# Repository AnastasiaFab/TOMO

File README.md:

#### TOMO is a programmable Touch Synthesizer board based on Arduino. 

##### TOMO can sense your touch on many different materials and create sounds to tell people things.

### What is TOMO?

##TO

**TO** means touch. Tomo uses **Swept Frequency Capacitive Sensing (SFCS)** a concept explored by [Disney Research Labs](http://www.disneyresearch.com/) on this [paper](http://www.disneyresearch.com/wp-content/uploads/touchechi2012.pdf). The Arduino implementation is based on the documentation by [ILLUTRON](http://illutron.dk/Instructable-Use-Any-Surface-as-a-Touch-Interface-with-Arduino) and developed by [Cleniem](https://github.com/clemniem). The internal ongoing research on SFCS can be found at [fablabbcn/TouchE](https://github.com/fablabbcn/TouchE).

##MO

**MO** means [Mozzi](http://sensorium.github.io/Mozzi/) an amazing library for sound synthesis library for Arduino developed by [Tim Barrass](http://www.reverberant.com/pp/barrass.htm). This means you can create sounds with it from simple tones to delays and echos. We will soon add *.WAV palying functionality too.

### How is TOMO?

* Small
* Portable
* Easy
* Fun
* and it runs on batteries for a week!

### Project team:

This project was developed with the support of the [EASTN (The European Art-Science-Technology Network)](https://github.com/eastn.eu) at [Fab Lab Barcelona](http://www.fablabbcn.org/). The first real setup was done for the [FAV Festival](http://festivaldesarchitecturesvives.com/) in Monpellier in June 2014.

* [Cleniem](https://github.com/clemniem) 
* [Pral2a](https://github.com/pral2s)
* [Anastasia Pistofidou](https://github.com/anastasiafab)

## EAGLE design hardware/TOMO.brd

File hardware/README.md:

The TOMO board
==============

Check the the Eagles and the PDF schematic for more information. 

Notice the PCB design is done to be milled on a PCB milling machine.

Check the CAM folder for the PNG for [FabModules](http://kokompe.cba.mit.edu/).

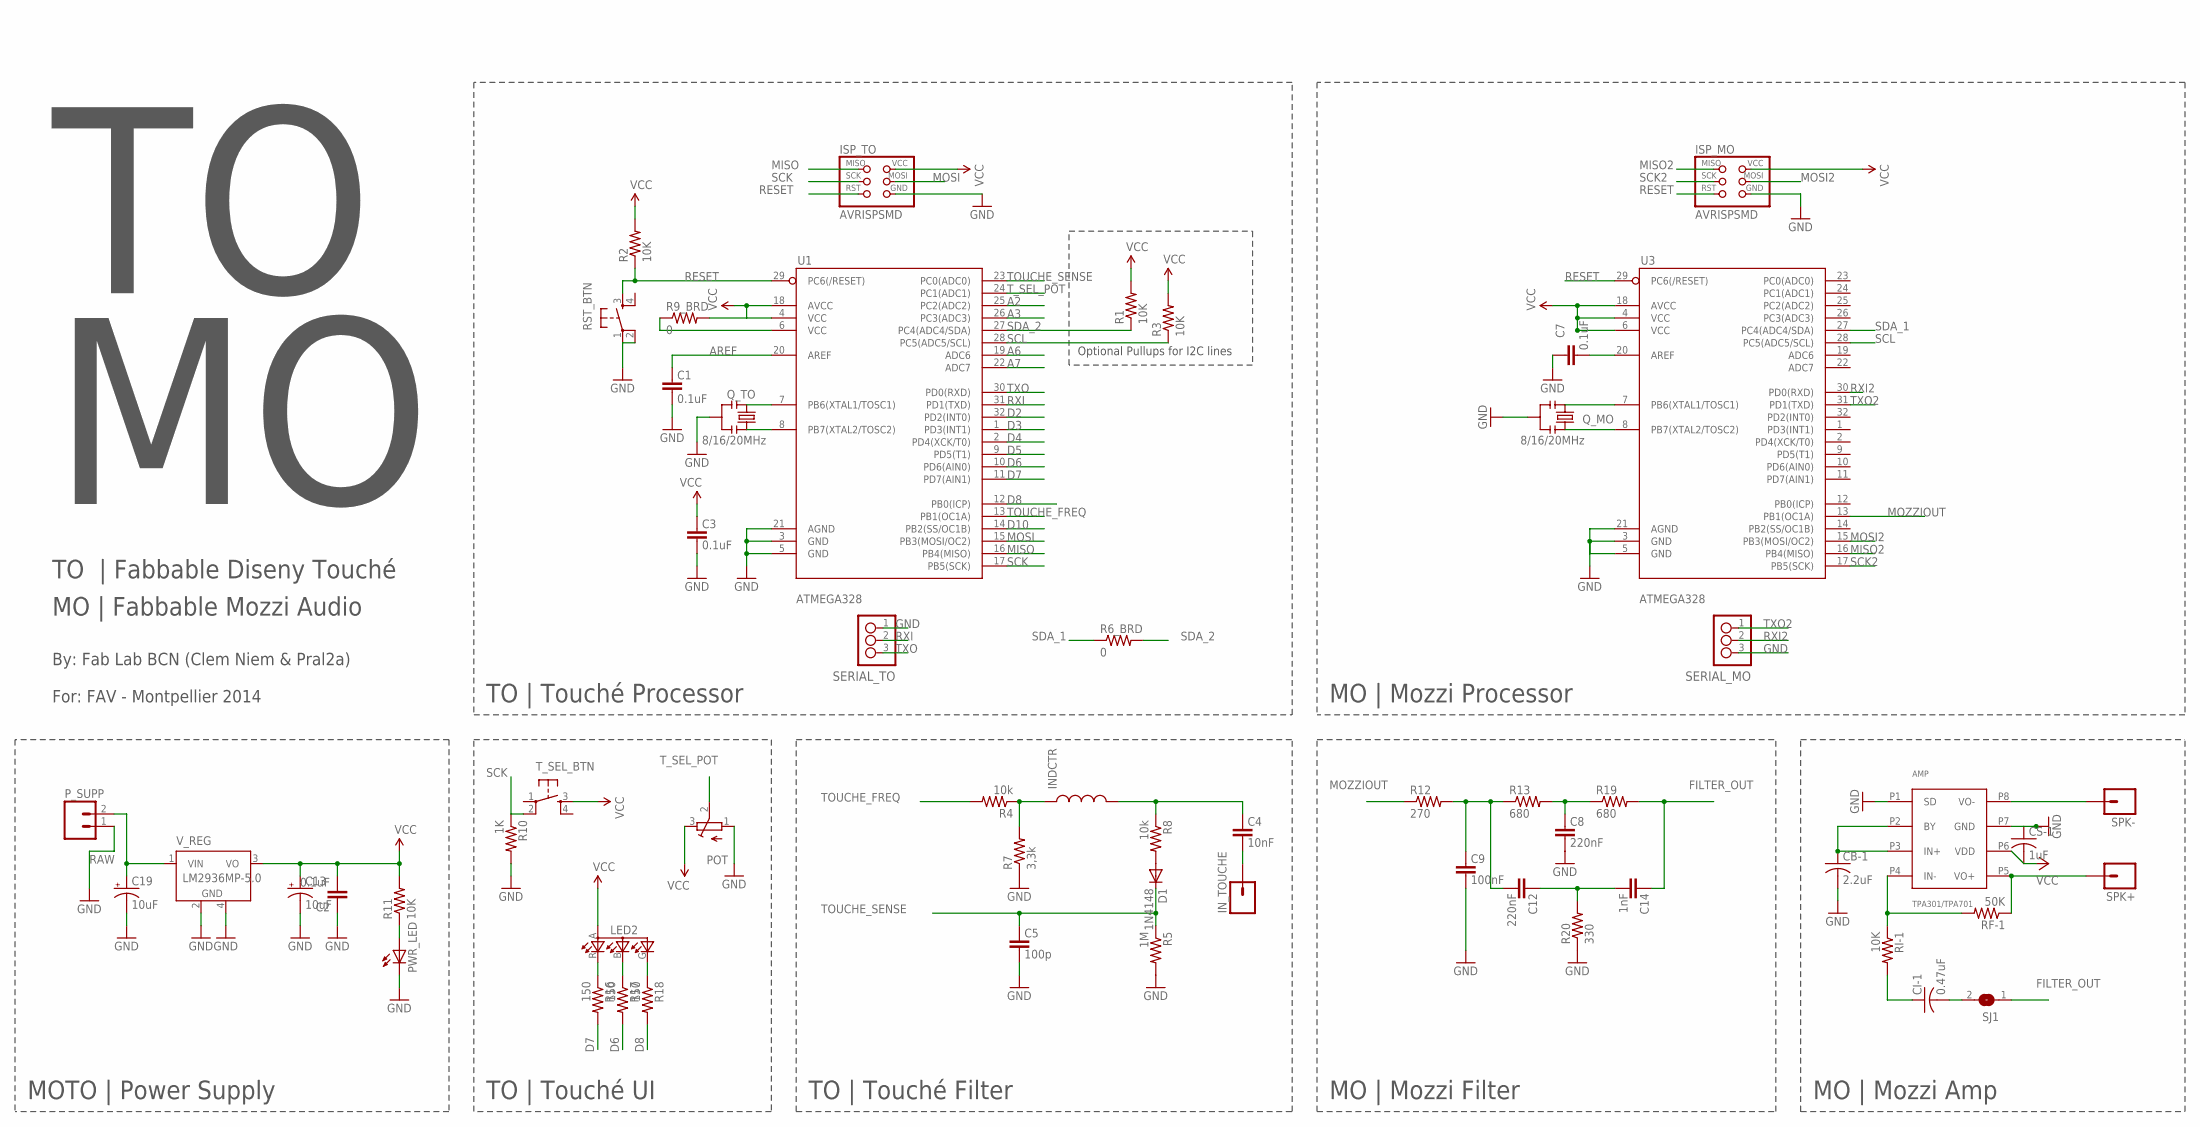
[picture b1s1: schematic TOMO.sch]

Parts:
AMP: TPA301/TPA701; SOIC8
C1, C2, C3, C7: 0.1uF; 1206
C4: 10nF; 1206
C5: 100p; 1206
C8, C12: 220nF; 1206
C9: 100nF; 1206
C13, C19: 10uF; EIA3216
C14: 1nF; 1206
CB-1: 2.2uF; C1206
CI-1: 0.47uF; C1206
CS-1: 1uF; C1206
D1: 1N4148; SOD123
INDCTR: INDUCTOR; CDRH3D28
IN_TOUCHE: M01PTH; 1X01
ISP_MO: AVRISPSMD; 2X03SMD
ISP_TO: AVRISPSMD; 2X03SMD
LED2: LEDRGBOLD; P-LCC-4-3
POT: TRIMPOTTC33X; TC33X
PWR_LED: LED1206; 1206
P_SUPP: M02PTH; 1X02
Q_MO: 8/16/20MHz; RESONATOR-SMD
Q_TO: 8/16/20MHz; RESONATOR-SMD
R1, R2, R3, R11: 10K; 1206
R4, R8: 10k; 1206
R5: 1M; 1206
R6_BRD, R9_BRD: 0; 1206
R7: 3,3k; 1206
R10: 1K; 1206
R12: 270; 1206
R13, R19: 680; 1206
R16, R17, R18: 150; 1206
R20: 330; 0603-RES
RF-1: 50K; R1206
RI-1: 10K; R1206
RST_BTN: 6MM_SWITCH6MM_SWITCH; 6MM_SWITCH
SERIAL_MO: 3_PIN_HEADERHEADER; SMT_PINS_3
SERIAL_TO: 3_PIN_HEADERHEADER; SMT_PINS_3
SJ1: SJW
SPK+: M01PTH; 1X01
SPK-: M01PTH; 1X01
T_SEL_BTN: 6MM_SWITCH6MM_SWITCH; 6MM_SWITCH
U1, U3: ATMEGA328; ATMEGA88THIN
V_REG: LM2936MP-5.0; SOT223

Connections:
A2: U1.25 (PC2(ADC2))
A3: U1.26 (PC3(ADC3))
A6: U1.19 (ADC6)
A7: U1.22 (ADC7)
AREF: C1.2, U1.20 (AREF)
D2: U1.32 (PD2(INT0))
D3: U1.1 (PD3(INT1))
D4: U1.2 (PD4(XCK/T0))
D5: U1.9 (PD5(T1))
D6: R17.2, U1.10 (PD6(AIN0))
D7: R16.2, U1.11 (PD7(AIN1))
D8: R18.2, U1.12 (PB0(ICP))
D10: U1.14 (PB2(SS/OC1B))
FILTER_OUT: C14.2, R19.2, SJ1.1
GND: AMP.P1 (SD), AMP.P7 (GND), C1.1, C2.1, C3.1, C5.1, C7.2, C8.1, C9.1, C13.C (-), C19.C (-), CB-1.2, CS-1.1, ISP_MO.6 (GND), ISP_TO.6 (GND), POT.1 (A), PWR_LED.2 (C), P_SUPP.1, Q_MO.2, Q_TO.2, R5.2, R7.1, R10.2, R20.1, RST_BTN.1, RST_BTN.2 (P1), SERIAL_MO.3, SERIAL_TO.1, U1.3 (GND), U1.5 (GND), U1.21 (AGND), U3.3 (GND), U3.5 (GND), U3.21 (AGND), V_REG.2 (GND), V_REG.4 (GND)
MISO: ISP_TO.1 (MISO), U1.16 (PB4(MISO))
MISO2: ISP_MO.1 (MISO), U3.16 (PB4(MISO))
MOSI: ISP_TO.4 (MOSI), U1.15 (PB3(MOSI/OC2))
MOSI2: ISP_MO.4 (MOSI), U3.15 (PB3(MOSI/OC2))
MOZZIOUT: R12.1, U3.13 (PB1(OC1A))
unnamed: Q_TO.1, U1.8 (PB7(XTAL2/TOSC2))
unnamed: CI-1.2, SJ1.2
unnamed: Q_TO.3, U1.7 (PB6(XTAL1/TOSC1))
unnamed: INDCTR.1, R4.1, R7.2
unnamed: C4.2, INDCTR.2, R8.1
unnamed: LED2.G (CGREEN), R18.1
unnamed: D1.ANODE (A), R8.2
unnamed: Q_MO.3, U3.7 (PB6(XTAL1/TOSC1))
unnamed: Q_MO.1, U3.8 (PB7(XTAL2/TOSC2))
unnamed: C12.2, C14.1, R20.2
unnamed: C4.1, IN_TOUCHE.1
unnamed: CI-1.1, RI-1.2
unnamed: LED2.R (CRED), R16.1
unnamed: C7.1, U3.20 (AREF)
unnamed: C9.2, C12.1, R12.2, R13.1
unnamed: LED2.B (CBLUE), R17.1
unnamed: R9_BRD.1, U1.6 (VCC)
unnamed: AMP.P4 (IN-), RF-1.2, RI-1.1
unnamed: C8.2, R13.2, R19.1
unnamed: AMP.P2 (BY), AMP.P3 (IN+), CB-1.1
unnamed: PWR_LED.1 (A), R11.1
RAW: C19.A (+), P_SUPP.2, V_REG.1 (VIN)
RESET: ISP_MO.5 (RST), ISP_TO.5 (RST), R2.1, RST_BTN.3 (S), U1.29 (PC6(/RESET)), U3.29 (PC6(/RESET))
RXI: SERIAL_TO.2, U1.31 (PD1(TXD))
RXI2: SERIAL_MO.2, U3.30 (PD0(RXD))
SCK: ISP_TO.3 (SCK), R10.1, T_SEL_BTN.2 (P1), U1.17 (PB5(SCK))
SCK2: ISP_MO.3 (SCK), U3.17 (PB5(SCK))
SCL: R3.1, U1.28 (PC5(ADC5/SCL)), U3.28 (PC5(ADC5/SCL))
SDA_1: R6_BRD.1, U3.27 (PC4(ADC4/SDA))
SDA_2: R1.1, R6_BRD.2, U1.27 (PC4(ADC4/SDA))
SPK_L+: AMP.P5 (VO+), RF-1.1, SPK+.1
SPK_L-: AMP.P8 (VO-), SPK-.1
TOUCHE_FREQ: R4.2, U1.13 (PB1(OC1A))
TOUCHE_SENSE: C5.2, D1.CATHODE (C), R5.1, U1.23 (PC0(ADC0))
TXO: SERIAL_TO.3, U1.30 (PD0(RXD))
TXO2: SERIAL_MO.1, U3.31 (PD1(TXD))
T_SEL_POT: POT.2 (S), U1.24 (PC1(ADC1))
VCC: AMP.P6 (VDD), C2.2, C3.2, C13.A (+), CS-1.2, ISP_MO.2 (VCC), ISP_TO.2 (VCC), LED2.A (A2), POT.3 (E), R1.2, R2.2, R3.2, R9_BRD.2, R11.2, T_SEL_BTN.3 (S), U1.4 (VCC), U1.18 (AVCC), U3.4 (VCC), U3.6 (VCC), U3.18 (AVCC), V_REG.3 (VO)

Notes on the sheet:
Optional Pullups for I2C lines
TO | Touché Filter
TO | Touché Processor
MO | Mozzi Processor
TO | Touché UI
MO | Mozzi Filter
MO | Mozzi Amp
MOTO | Power Supply
TO | Fabbable Diseny Touché
MO | Fabbable Mozzi Audio
By: Fab Lab BCN (Clem Niem & Pral2a)
For: FAV - Montpellier 2014

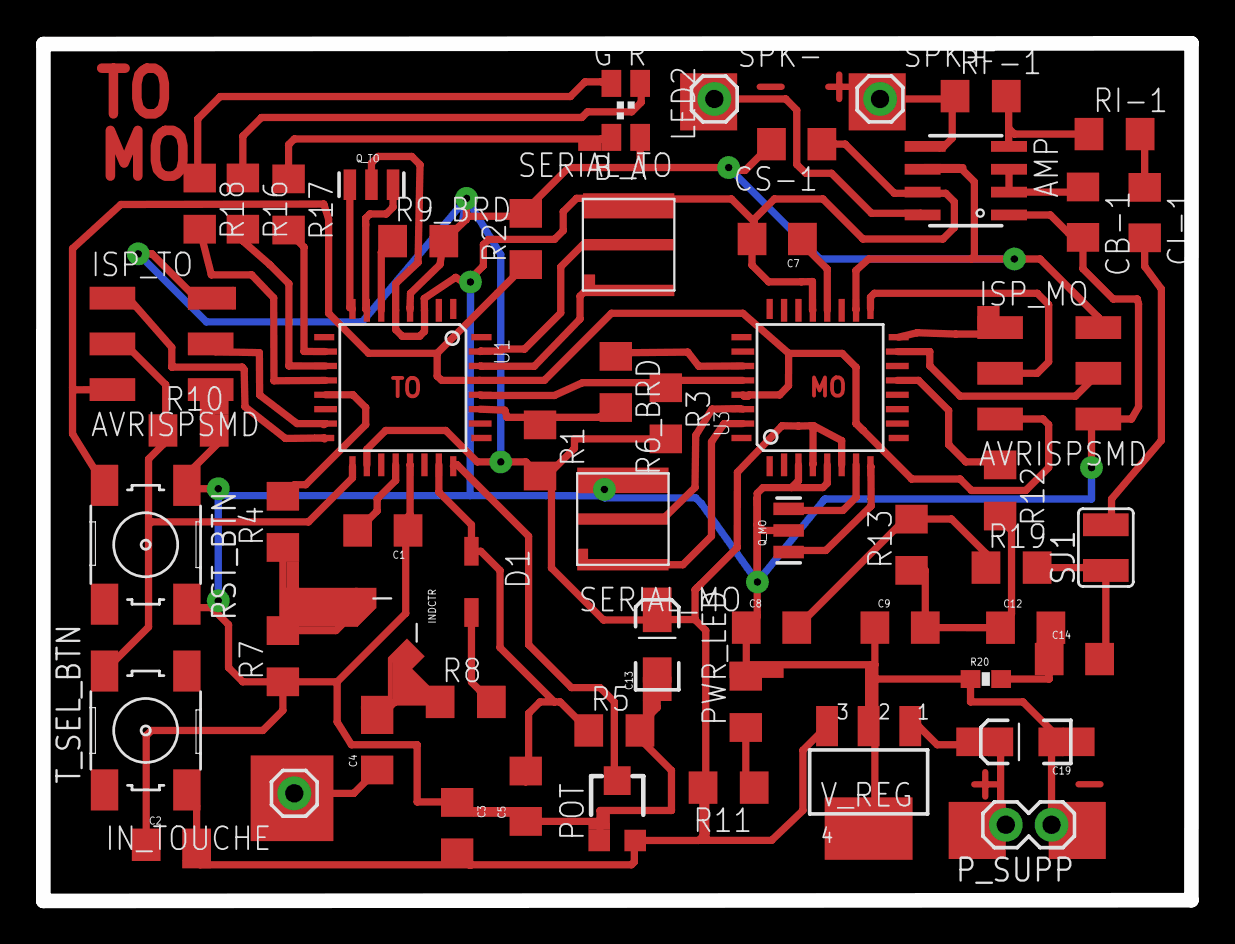
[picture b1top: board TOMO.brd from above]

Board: 2 copper layers, 63.8 x 47.6 mm, 57 parts (0 on the bottom side), 49 nets.

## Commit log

2014-08-03 TOMO is alive
2014-08-03 Some pictures
2014-08-03 Small changes
2014-08-04 Details
2014-08-04 Correcting some wrong namings
2014-08-04 Logo changes

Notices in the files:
parts and their libraries:
01_SparkFun: Licensing: CC v3.0 Share-Alike You are welcome to use this library for commercial purposes.
